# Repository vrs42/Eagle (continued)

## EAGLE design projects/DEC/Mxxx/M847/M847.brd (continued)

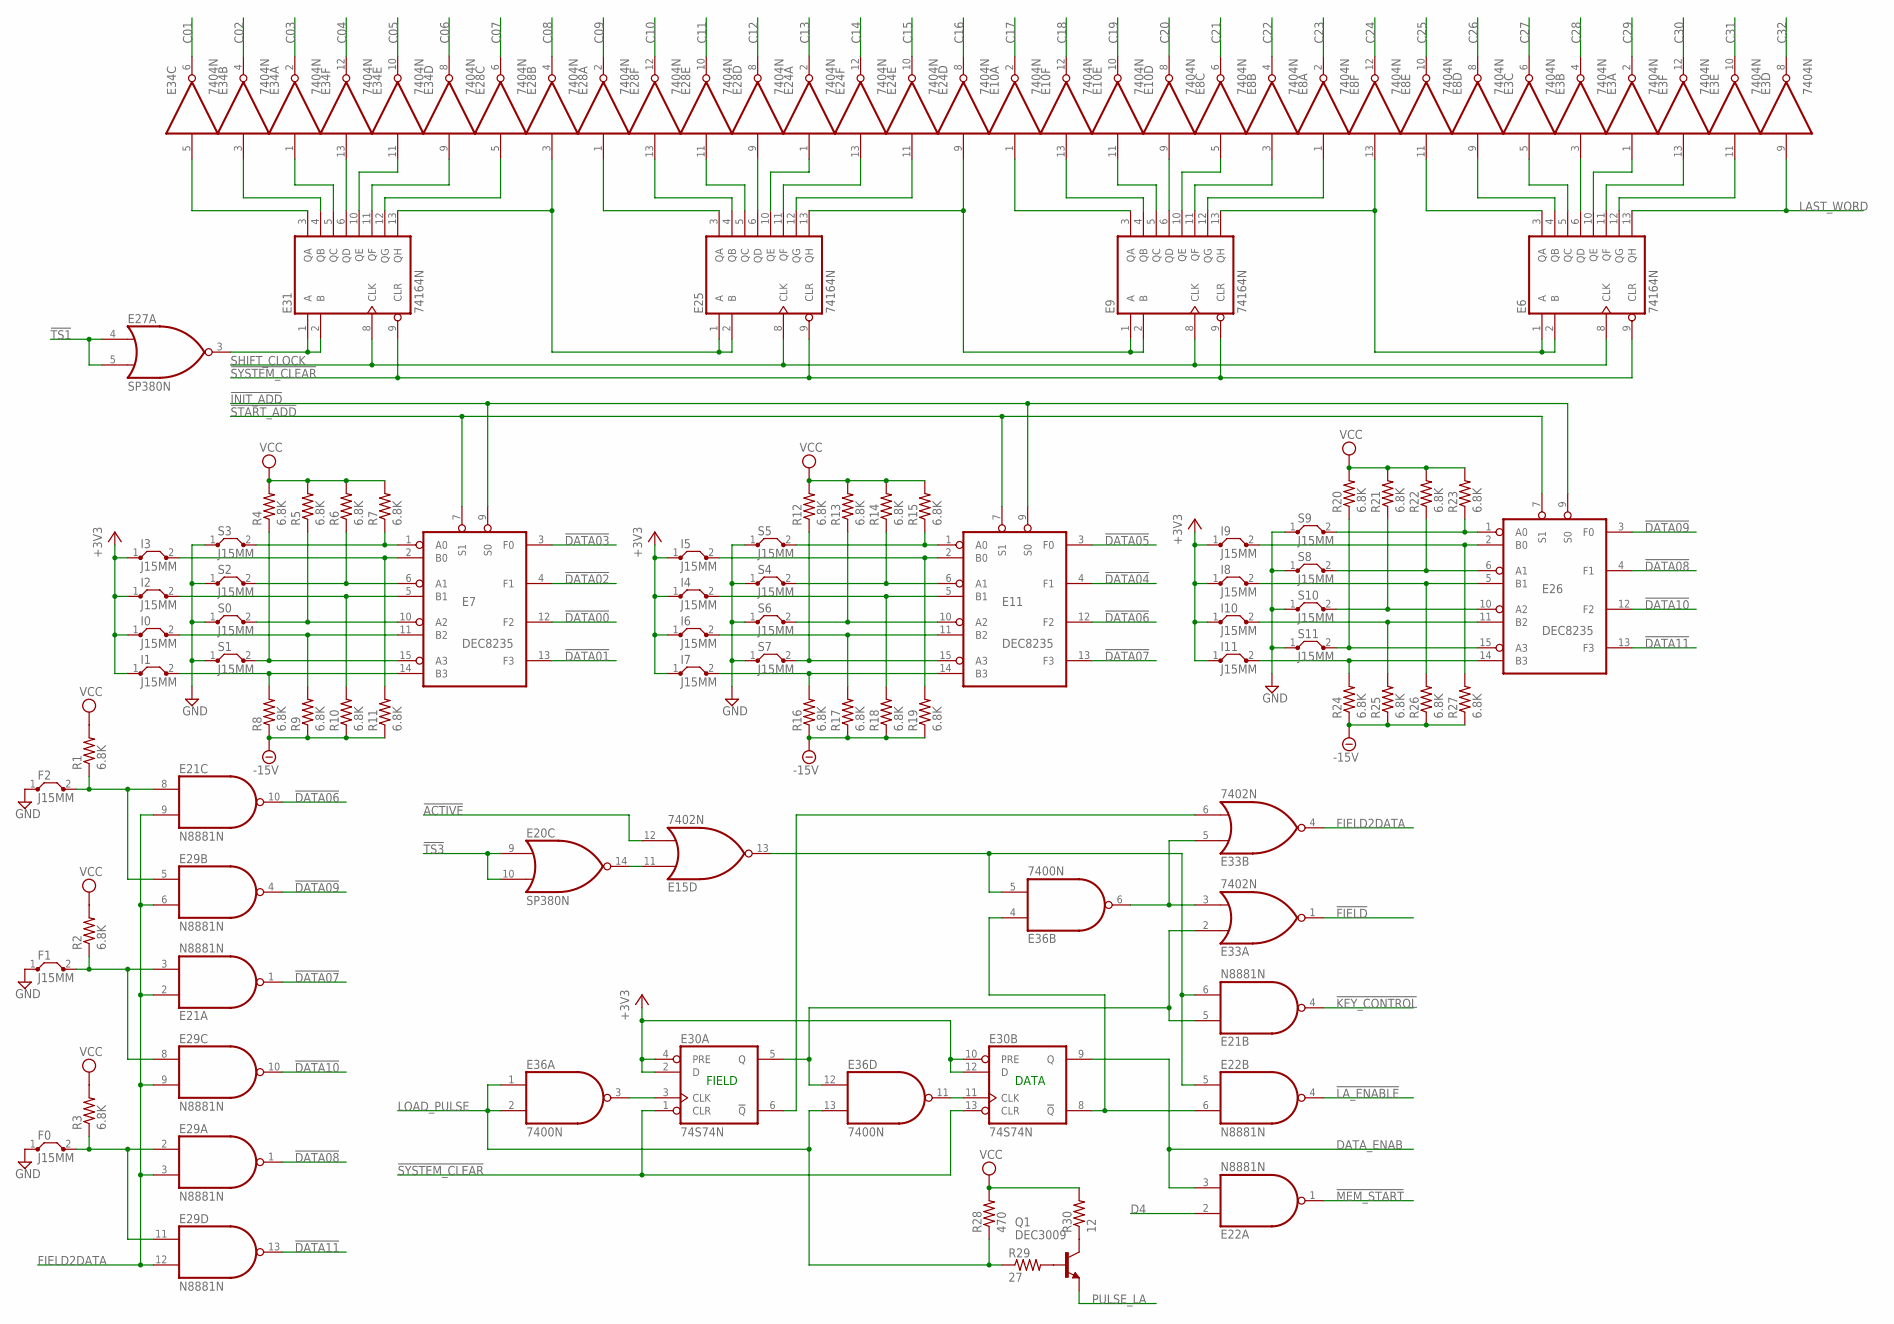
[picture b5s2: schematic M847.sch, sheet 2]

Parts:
E3, E8, E10, E24, E28, E34: 7404N; DIL14
E6, E9, E25, E31: 74164N; DIL14
E7, E11, E26: DEC8235; DIL16
E15, E33: 7402N; DIL14
E20, E27: SP380N; DIL14
E21, E22, E29: N8881N; DIL14
E30: 74S74N; DIL14
E36: 7400N; DIL14
F0, F1, F2: J15MM; 15
I0, I1, I2, I3, I4, I5, I6, I7, I8, I9, I10, I11: J15MM; 15
Q1: DEC3009; TO92
R1, R2, R3, R4, R5, R6, R7, R8, R9, R10, R11, R12, R13, R14, R15, R16, R17, R18, R19, R20, R21, R22, R23, R24, R25, R26, R27: 6.8K; 0207/10
R28: 470; 0207/10
R29: 27; 0207/10
R30: 12; 0207/10
S0, S1, S2, S3, S4, S5, S6, S7, S8, S9, S10, S11: J15MM; 15

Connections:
!ACTIVE: E15.12 (I1); also elsewhere on the board
!DATA00: E7.12 (F2); also elsewhere on the board
!DATA01: E7.13 (F3); also elsewhere on the board
!DATA02: E7.4 (F1); also elsewhere on the board
!DATA03: E7.3 (F0); also elsewhere on the board
!DATA04: E11.4 (F1); also elsewhere on the board
!DATA05: E11.3 (F0); also elsewhere on the board
!DATA06: E11.12 (F2), E21.10 (O); also elsewhere on the board
!DATA07: E11.13 (F3), E21.1 (O); also elsewhere on the board
!DATA08: E26.4 (F1), E29.1 (O); also elsewhere on the board
!DATA09: E26.3 (F0), E29.4 (O); also elsewhere on the board
!DATA10: E26.12 (F2), E29.10 (O); also elsewhere on the board
!DATA11: E26.13 (F3), E29.13 (O); also elsewhere on the board
!DATA_EN: E22.6 (I1), E30.8 (!Q), E36.4 (I0)
!FIELD: E33.1 (O); also elsewhere on the board
!FIELD_EN: E30.6 (!Q), E33.6 (I1)
!INIT_ADD: E7.9 (S0), E11.9 (S0), E26.9 (S0); also elsewhere on the board
!KEY_CONTROL: E21.4 (O); also elsewhere on the board
!LA_ENABLE: E22.4 (O); also elsewhere on the board
!MEM_START: E22.1 (O); also elsewhere on the board
!START_ADD: E7.7 (S1), E11.7 (S1), E26.7 (S1); also elsewhere on the board
!SYSTEM_CLEAR: E6.9 (CLR), E9.9 (CLR), E25.9 (CLR), E30.1 (CLR), E30.13 (CLR), E31.9 (CLR); also elsewhere on the board
!TS1: E27.4 (I0), E27.5 (I1); also elsewhere on the board
!TS3: E20.9 (I0), E20.10 (I1); also elsewhere on the board
+3V3: E30.2 (D), E30.4 (PRE), E30.10 (PRE), E30.12 (D), I0.1, I1.1, I2.1, I3.1, I4.1, I5.1, I6.1, I7.1, I8.1, I9.1, I10.1, I11.1; also elsewhere on the board
-15V: R8.1, R9.1, R10.1, R11.1, R16.1, R17.1, R18.1, R19.1, R24.1, R25.1, R26.1, R27.1; also elsewhere on the board
C01: E34.6 (O); also elsewhere on the board
C02: E34.4 (O); also elsewhere on the board
C03: E34.2 (O); also elsewhere on the board
C04: E34.12 (O); also elsewhere on the board
C05: E34.10 (O); also elsewhere on the board
C06: E34.8 (O); also elsewhere on the board
C07: E28.6 (O); also elsewhere on the board
C08: E28.4 (O); also elsewhere on the board
C09: E28.2 (O); also elsewhere on the board
C10: E28.12 (O); also elsewhere on the board
C11: E28.10 (O); also elsewhere on the board
C12: E28.8 (O); also elsewhere on the board
C13: E24.2 (O); also elsewhere on the board
C14: E24.12 (O); also elsewhere on the board
C15: E24.10 (O); also elsewhere on the board
C16: E24.8 (O); also elsewhere on the board
C17: E10.2 (O); also elsewhere on the board
C18: E10.12 (O); also elsewhere on the board
C19: E10.10 (O); also elsewhere on the board
C20: E10.8 (O); also elsewhere on the board
C21: E8.6 (O); also elsewhere on the board
C22: E8.4 (O); also elsewhere on the board
C23: E8.2 (O); also elsewhere on the board
C24: E8.12 (O); also elsewhere on the board
C25: E8.10 (O); also elsewhere on the board
C26: E8.8 (O); also elsewhere on the board
C27: E3.6 (O); also elsewhere on the board
C28: E3.4 (O); also elsewhere on the board
C29: E3.2 (O); also elsewhere on the board
C30: E3.12 (O); also elsewhere on the board
C31: E3.10 (O); also elsewhere on the board
C32: E3.8 (O); also elsewhere on the board
D4: E22.2 (I0); also elsewhere on the board
DATA_ENAB: E22.3 (I1), E30.9 (Q); also elsewhere on the board
FIELD2DATA: E21.2 (I0), E21.9 (I1), E29.3 (I1), E29.6 (I1), E29.9 (I1), E29.12 (I1), E33.4 (O)
FIELD_EN: E21.5 (I0), E30.5 (Q), E33.2 (I0), E36.12 (I0)
GND: E3.7 (GND), E6.7 (GND), E7.8 (GND), E8.7 (GND), E9.7 (GND), E10.7 (GND), E11.8 (GND), E15.7 (GND), E20.1 (GND), E21.7 (GND), E22.7 (GND), E24.7 (GND), E25.7 (GND), E26.8 (GND), E27.1 (GND), E28.7 (GND), E29.7 (GND), E30.7 (GND), E31.7 (GND), E33.7 (GND), E34.7 (GND), E36.7 (GND), F0.1, F1.1, F2.1, S0.1, S1.1, S2.1, S3.1, S4.1, S5.1, S6.1, S7.1, S8.1, S9.1, S10.1, S11.1; also elsewhere on the board
LAST_WORD: E3.9 (I), E6.13 (QH); also elsewhere on the board
LOAD_PULSE: E36.1 (I0), E36.2 (I1), E36.13 (I1), R28.1, R29.1; also elsewhere on the board
unnamed: E7.1 (A0), R7.1, S3.2
unnamed: E21.8 (I0), E29.5 (I0), F2.2, R1.1
unnamed: E21.3 (I1), E29.8 (I0), F1.2, R2.1
unnamed: E29.2 (I0), E29.11 (I0), F0.2, R3.1
unnamed: E7.6 (A1), R6.1, S2.2
unnamed: E7.10 (A2), R5.1, S0.2
unnamed: E7.15 (A3), R4.1, S1.2
unnamed: E7.14 (B3), I1.2, R8.2
unnamed: E7.11 (B2), I0.2, R9.2
unnamed: E7.5 (B1), I2.2, R10.2
unnamed: E7.2 (B0), I3.2, R11.2
unnamed: E11.1 (A0), R15.1, S5.2
unnamed: E11.6 (A1), R14.1, S4.2
unnamed: E11.10 (A2), R13.1, S6.2
unnamed: E11.15 (A3), R12.1, S7.2
unnamed: E11.14 (B3), I7.2, R16.2
unnamed: E11.11 (B2), I6.2, R17.2
unnamed: E11.5 (B1), I4.2, R18.2
unnamed: E11.2 (B0), I5.2, R19.2
unnamed: E26.1 (A0), R23.1, S9.2
unnamed: E26.6 (A1), R22.1, S8.2
unnamed: E26.10 (A2), R21.1, S10.2
unnamed: E26.15 (A3), R20.1, S11.2
unnamed: E26.14 (B3), I11.2, R24.2
unnamed: E26.11 (B2), I10.2, R25.2
unnamed: E26.5 (B1), I8.2, R26.2
unnamed: E26.2 (B0), I9.2, R27.2
unnamed: Q1.3 (C), R30.1
unnamed: E31.3 (QA), E34.5 (I)
unnamed: Q1.2 (B), R29.2
unnamed: E30.11 (CLK), E36.11 (O)
unnamed: E30.3 (CLK), E36.3 (O)
unnamed: E15.13 (O), E21.6 (I1), E22.5 (I0), E36.5 (I1)
unnamed: E31.6 (QD), E34.13 (I)
unnamed: E9.5 (QC), E10.11 (I)
unnamed: E9.6 (QD), E10.9 (I)
unnamed: E3.3 (I), E6.6 (QD)
unnamed: E31.4 (QB), E34.3 (I)
unnamed: E31.5 (QC), E34.1 (I)
unnamed: E31.10 (QE), E34.11 (I)
unnamed: E31.11 (QF), E34.9 (I)
unnamed: E28.5 (I), E31.12 (QG)
unnamed: E25.3 (QA), E28.1 (I)
unnamed: E25.4 (QB), E28.13 (I)
unnamed: E25.5 (QC), E28.11 (I)
unnamed: E25.6 (QD), E28.9 (I)
unnamed: E24.1 (I), E25.10 (QE)
unnamed: E9.3 (QA), E10.1 (I)
unnamed: E6.3 (QA), E8.11 (I)
unnamed: E3.11 (I), E6.12 (QG)
unnamed: E3.13 (I), E6.11 (QF)
unnamed: E3.1 (I), E6.10 (QE)
unnamed: E24.13 (I), E25.11 (QF)
unnamed: E24.11 (I), E25.12 (QG)
unnamed: E9.4 (QB), E10.13 (I)
unnamed: E8.5 (I), E9.10 (QE)
unnamed: E8.3 (I), E9.11 (QF)
unnamed: E8.1 (I), E9.12 (QG)
unnamed: E6.4 (QB), E8.9 (I)
unnamed: E3.5 (I), E6.5 (QC)
unnamed: E6.1 (A), E6.2 (B), E8.13 (I), E9.13 (QH)
unnamed: E9.1 (A), E9.2 (B), E24.9 (I), E25.13 (QH)
unnamed: E25.1 (A), E25.2 (B), E28.3 (I), E31.13 (QH)
unnamed: E33.3 (I1), E33.5 (I0), E36.6 (O)
unnamed: E15.11 (I0), E20.14 (O)
PULSE_LA: Q1.1 (E); also elsewhere on the board
SHIFT_CLOCK: E6.8 (CLK), E9.8 (CLK), E25.8 (CLK), E31.8 (CLK); also elsewhere on the board
TS1: E27.3 (O), E31.1 (A), E31.2 (B)
VCC: E3.14 (VCC), E6.14 (VCC), E7.16 (VCC), E8.14 (VCC), E9.14 (VCC), E10.14 (VCC), E11.16 (VCC), E15.14 (VCC), E20.8 (VCC), E21.14 (VCC), E22.14 (VCC), E24.14 (VCC), E25.14 (VCC), E26.16 (VCC), E27.8 (VCC), E28.14 (VCC), E29.14 (VCC), E30.14 (VCC), E31.14 (VCC), E33.14 (VCC), E34.14 (VCC), E36.14 (VCC), R1.2, R2.2, R3.2, R4.2, R5.2, R6.2, R7.2, R12.2, R13.2, R14.2, R15.2, R20.2, R21.2, R22.2, R23.2, R28.2, R30.2; also elsewhere on the board

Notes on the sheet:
DATA
FIELD

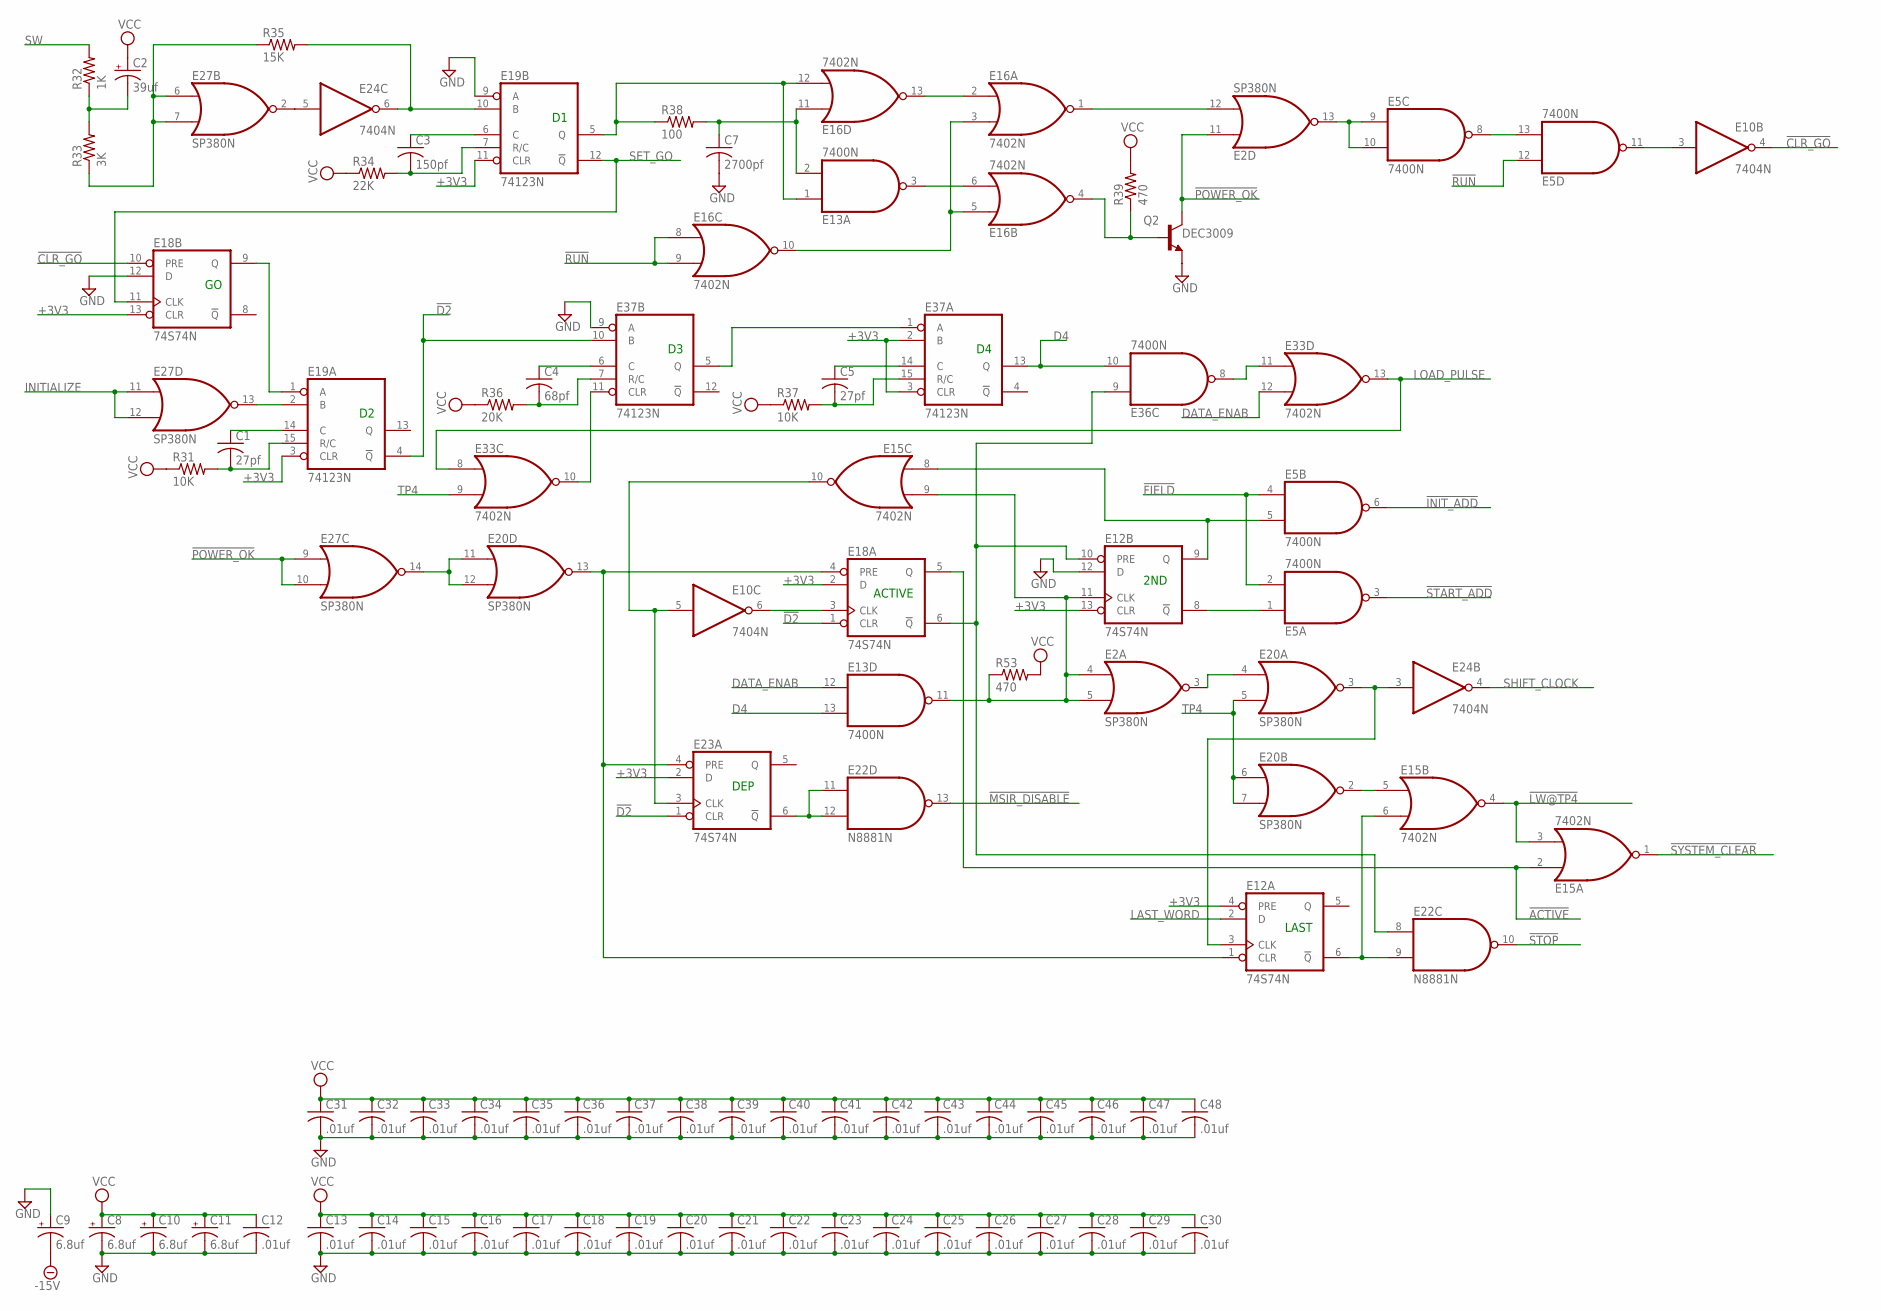
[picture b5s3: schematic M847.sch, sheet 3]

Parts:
C1, C5: 27pf; C050-025X075
C2: 39uf; E15-5
C3: 150pf; C050-025X075
C4: 68pf; C050-025X075
C7: 2700pf; C102-043X133
C8, C9, C10, C11: 6.8uf; E15-5
C12, C13, C14, C15, C16, C17, C18, C19, C20, C21, C22, C23, C24, C25, C26, C27, C28, C29, C30, C31, C32, C33, C34, C35, C36, C37, C38, C39, C40, C41, C42, C43, C44, C45, C46, C47, C48: .01uf; C050-025X075
E2, E20, E27: SP380N; DIL14
E5, E13, E36: 7400N; DIL14
E10, E24: 7404N; DIL14
E12, E18, E23: 74S74N; DIL14
E15, E16, E33: 7402N; DIL14
E19, E37: 74123N; DIL16
E22: N8881N; DIL14
Q2: DEC3009; TO92
R31, R37: 10K; 0207/10
R32: 1K; 0207/10
R33: 3K; 0207/10
R34: 22K; 0207/10
R35: 15K; 0207/10
R36: 20K; 0207/10
R38: 100; 0207/10
R39, R53: 470; 0207/10

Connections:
!ACTIVE: E15.2 (I0), E18.5 (Q); also elsewhere on the board
!CLR_D3: E33.10 (O), E37.11 (CLR)
!CLR_GO: E10.4 (O), E18.10 (PRE)
!D2: E18.1 (CLR), E19.4 (!Q), E23.1 (CLR), E37.10 (B)
!DEP: E22.11 (I0), E22.12 (I1), E23.6 (!Q)
!FIELD: E5.2 (I1), E5.4 (I0); also elsewhere on the board
!GO: E18.9 (Q), E19.1 (A)
!INIT_ADD: E5.6 (O); also elsewhere on the board
!LAST: E12.6 (!Q), E15.6 (I1), E22.9 (I1)
!LW@TP4: E15.3 (I1), E15.4 (O)
!MSIR_DISABLE: E22.13 (O); also elsewhere on the board
!POWER_OK: E2.11 (I0), E27.9 (I0), E27.10 (I1), Q2.3 (C); also elsewhere on the board
!RUN: E5.12 (I0), E16.8 (I0), E16.9 (I1); also elsewhere on the board
!START_ADD: E5.3 (O); also elsewhere on the board
!STOP: E22.10 (O); also elsewhere on the board
!SYSTEM_CLEAR: E15.1 (O); also elsewhere on the board
+3V3: E12.4 (PRE), E12.13 (CLR), E18.2 (D), E18.13 (CLR), E19.3 (CLR), E19.11 (CLR), E23.2 (D), E37.2 (B), E37.3 (CLR); also elsewhere on the board
-15V: C9.-; also elsewhere on the board
ACTIVE: E12.10 (PRE), E18.6 (!Q), E22.8 (I0), E36.9 (I0)
D1_DELAYED: C7.1, E13.2 (I1), E16.11 (I0), R38.2
D4: E13.13 (I1), E36.10 (I1), E37.13 (Q); also elsewhere on the board
DATA_ENAB: E13.12 (I0), E33.12 (I1); also elsewhere on the board
GND: C7.2, C8.-, C9.+, C10.-, C11.-, C12.2, C13.2, C14.2, C15.2, C16.2, C17.2, C18.2, C19.2, C20.2, C21.2, C22.2, C23.2, C24.2, C25.2, C26.2, C27.2, C28.2, C29.2, C30.2, C31.2, C32.2, C33.2, C34.2, C35.2, C36.2, C37.2, C38.2, C39.2, C40.2, C41.2, C42.2, C43.2, C44.2, C45.2, C46.2, C47.2, C48.2, E2.1 (GND), E5.7 (GND), E10.7 (GND), E12.7 (GND), E12.12 (D), E13.7 (GND), E15.7 (GND), E16.7 (GND), E18.7 (GND), E18.12 (D), E19.8 (GND), E19.9 (A), E20.1 (GND), E22.7 (GND), E23.7 (GND), E24.7 (GND), E27.1 (GND), E33.7 (GND), E36.7 (GND), E37.8 (GND), E37.9 (A), Q2.1 (E); also elsewhere on the board
INITIALIZE: E27.11 (I0), E27.12 (I1); also elsewhere on the board
LAST_WORD: E12.2 (D); also elsewhere on the board
LOAD_PULSE: E33.8 (I0), E33.13 (O); also elsewhere on the board
unnamed: E19.2 (B), E27.13 (O)
unnamed: E10.6 (O), E18.3 (CLK)
unnamed: C1.1, E19.14 (C)
unnamed: C1.2, E19.15 (R/C), R31.2
unnamed: C3.1, E19.6 (C)
unnamed: C2.-, R32.1, R33.2
unnamed: E27.6 (I0), E27.7 (I1), R33.1, R35.1
unnamed: E24.5 (I), E27.2 (O)
unnamed: E19.10 (B), E24.6 (O), R35.2
unnamed: C3.2, E19.7 (R/C), R34.2
unnamed: C4.2, E37.7 (R/C), R36.2
unnamed: C4.1, E37.6 (C)
unnamed: C5.1, E37.14 (C)
unnamed: C5.2, E37.15 (R/C), R37.2
unnamed: E37.1 (A), E37.5 (Q)
unnamed: E13.1 (I0), E16.12 (I1), E19.5 (Q), R38.1
unnamed: E16.2 (I0), E16.13 (O)
unnamed: E13.3 (O), E16.6 (I1)
unnamed: E2.12 (I1), E16.1 (O)
unnamed: E2.13 (O), E5.9 (I0), E5.10 (I1)
unnamed: E16.4 (O), Q2.2 (B), R39.1
unnamed: E5.8 (O), E5.13 (I1)
unnamed: E5.11 (O), E10.3 (I)
unnamed: E33.11 (I0), E36.8 (O)
unnamed: E12.1 (CLR), E18.4 (PRE), E20.13 (O), E23.4 (PRE)
unnamed: E20.11 (I0), E20.12 (I1), E27.14 (O)
unnamed: E2.4 (I0), E2.5 (I1), E12.11 (CLK), E13.11 (O), E15.9 (I1), R53.1
unnamed: E12.3 (CLK), E20.3 (O), E24.3 (I)
unnamed: E5.5 (I1), E12.9 (Q), E15.8 (I0)
unnamed: E5.1 (I0), E12.8 (!Q)
unnamed: E15.5 (I0), E20.2 (O)
unnamed: E2.3 (O), E20.4 (I0)
unnamed: E10.5 (I), E15.10 (O), E23.3 (CLK)
RUN: E16.3 (I1), E16.5 (I0), E16.10 (O)
SET_GO: E18.11 (CLK), E19.12 (!Q)
SHIFT_CLOCK: E24.4 (O); also elsewhere on the board
SW: R32.2; also elsewhere on the board
TP4: E20.5 (I1), E20.6 (I0), E20.7 (I1), E33.9 (I1); also elsewhere on the board
VCC: C2.+, C8.+, C10.+, C11.+, C12.1, C13.1, C14.1, C15.1, C16.1, C17.1, C18.1, C19.1, C20.1, C21.1, C22.1, C23.1, C24.1, C25.1, C26.1, C27.1, C28.1, C29.1, C30.1, C31.1, C32.1, C33.1, C34.1, C35.1, C36.1, C37.1, C38.1, C39.1, C40.1, C41.1, C42.1, C43.1, C44.1, C45.1, C46.1, C47.1, C48.1, E2.8 (VCC), E5.14 (VCC), E10.14 (VCC), E12.14 (VCC), E13.14 (VCC), E15.14 (VCC), E16.14 (VCC), E18.14 (VCC), E19.16 (VCC), E20.8 (VCC), E22.14 (VCC), E23.14 (VCC), E24.14 (VCC), E27.8 (VCC), E33.14 (VCC), E36.14 (VCC), E37.16 (VCC), R31.1, R34.1, R36.1, R37.1, R39.2, R53.2; also elsewhere on the board

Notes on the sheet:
2ND
LAST
ACTIVE
DEP

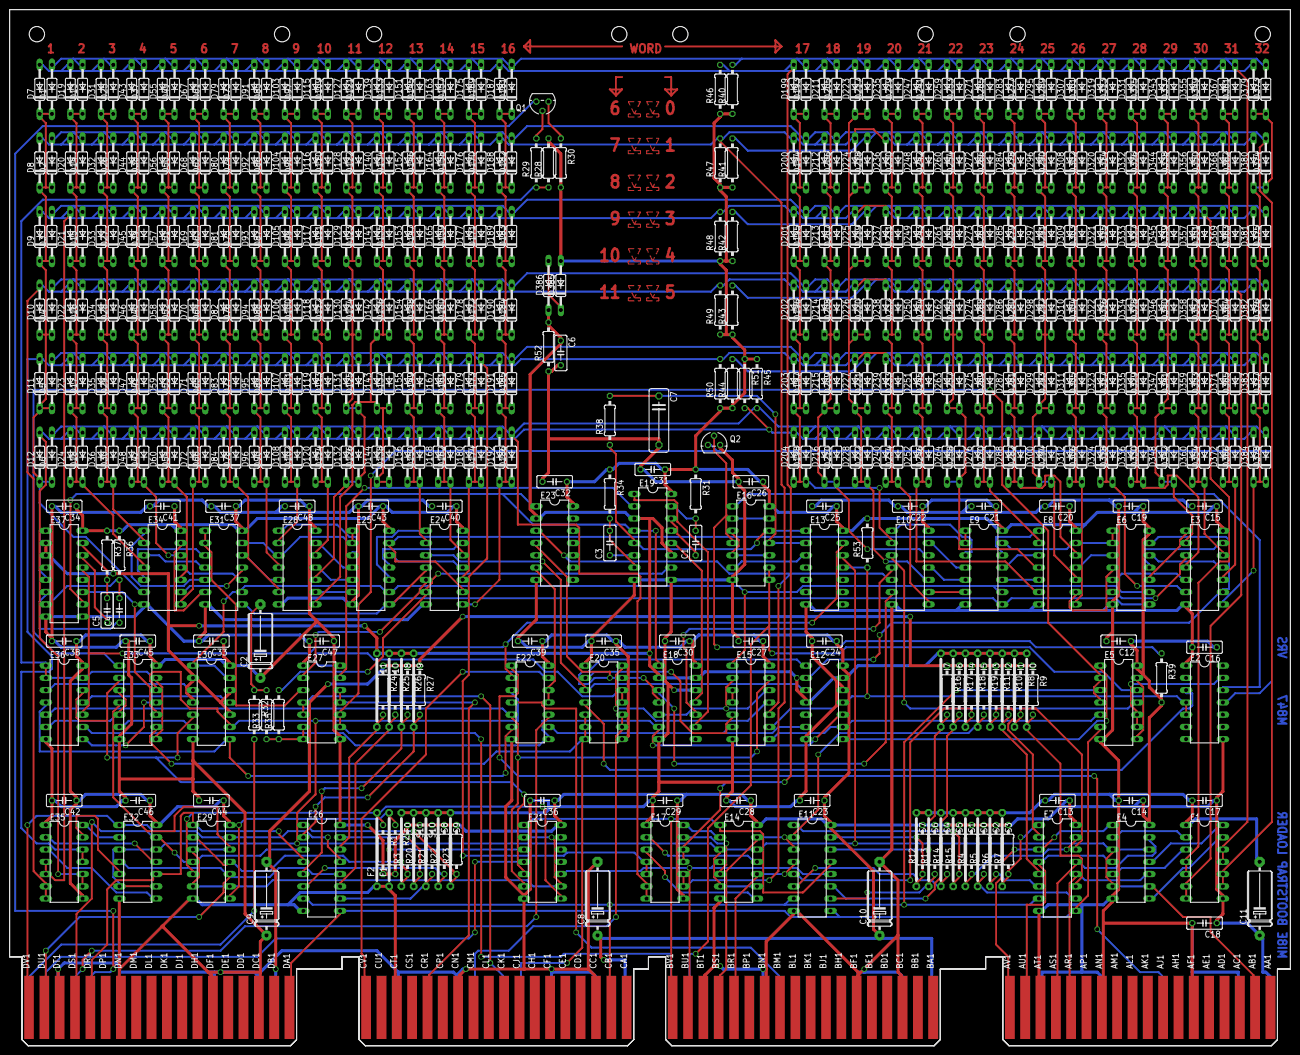
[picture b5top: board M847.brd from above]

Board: 2 copper layers, 265.3 x 214.6 mm, 555 parts (0 on the bottom side), 210 nets.
